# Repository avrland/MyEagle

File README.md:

# MyEagle
Personal Eagle library/projects folder

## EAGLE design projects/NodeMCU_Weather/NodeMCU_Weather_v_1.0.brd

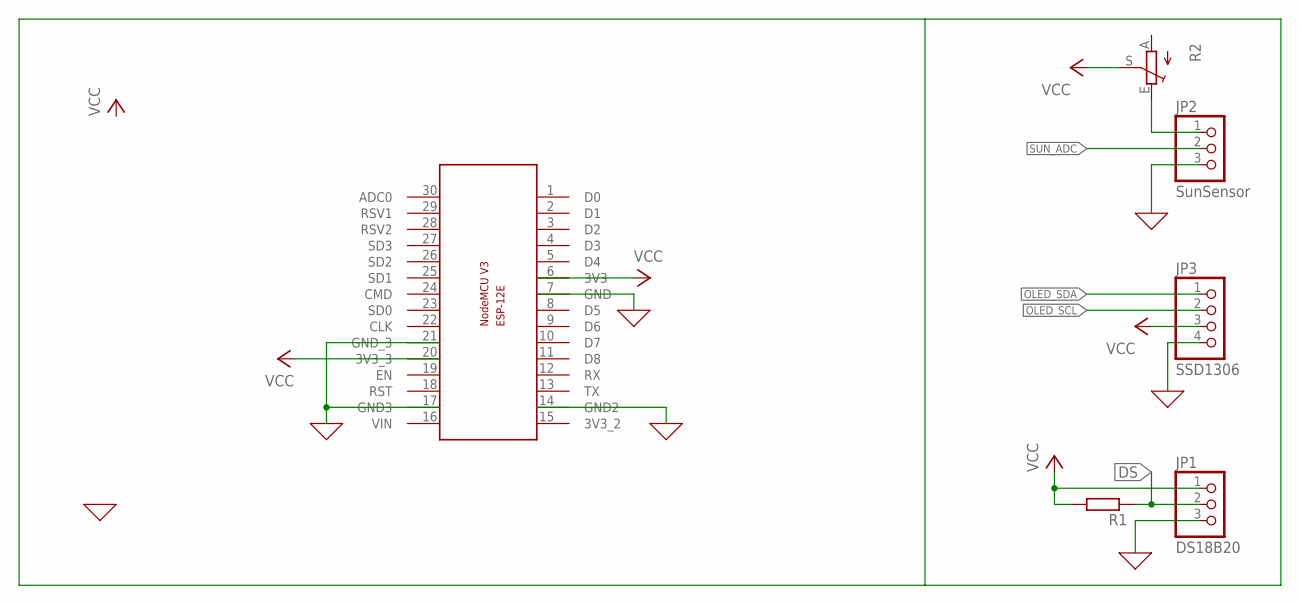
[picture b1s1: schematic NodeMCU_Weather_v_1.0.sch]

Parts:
JP1: DS18B20; 1X03
JP2: SunSensor; 1X03
JP3: SSD1306; 1X04
R1: R0204/7; 0204/7
R2: TRIM_EU-B25P; B25P
U$1: NODEMCUESP8266

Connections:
0: JP1.3, JP2.3, JP3.4, U$1.7 (GND), U$1.14 (GND2), U$1.17 (GND3), U$1.21 (GND_3)
DS: JP1.2, R1.1
unnamed: JP2.1, R2.E
OLED_SCL: JP3.2
OLED_SDA: JP3.1
SUN_ADC: JP2.2
VCC: JP1.1, JP3.3, R1.2, R2.S, U$1.6 (3V3), U$1.20 (3V3_3)

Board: 2 copper layers, 6 parts (0 on the bottom side), 4 nets, no tracks yet.

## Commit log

2022-04-06 Create LICENSE
2022-04-07 Base of nodemcu schematics and board
